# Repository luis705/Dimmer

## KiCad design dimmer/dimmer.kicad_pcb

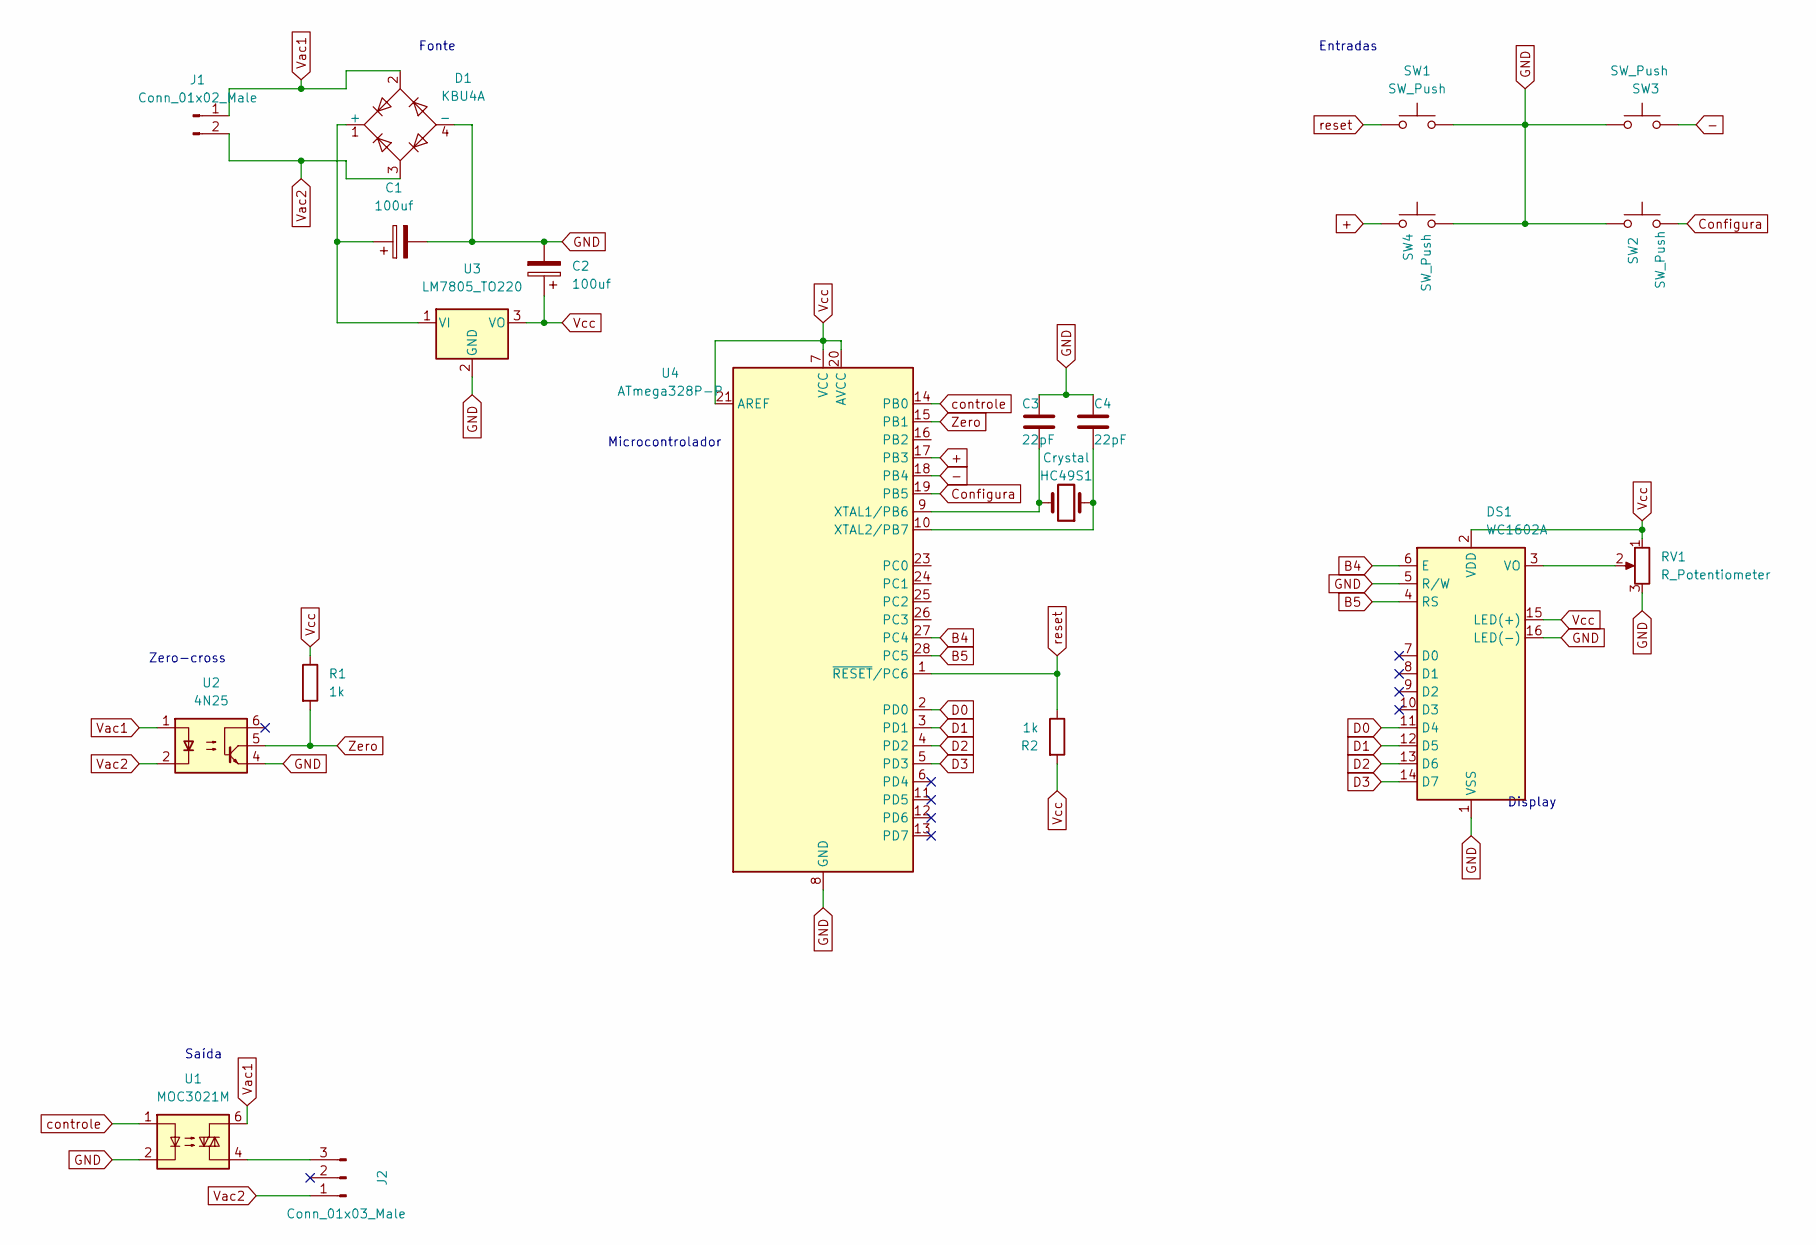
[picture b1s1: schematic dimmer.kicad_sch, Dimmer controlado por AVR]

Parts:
C1, C2: 100uf; CP_Radial_D8.0mm_P5.00mm
C3, C4: 22pF; C_Disc_D5.0mm_W2.5mm_P5.00mm
D1: KBU4A; Diode_Bridge_15.1x15.1x6.3mm_P10.9mm
DS1: WC1602A
HC49S1: Crystal; Crystal_HC49-4H_Vertical
J1: Conn_01x02_Male; Molex_KK-254_AE-6410-02A_1x02_P2.54mm_Vertical
J2: Conn_01x03_Male; FanPinHeader_1x03_P2.54mm_Vertical
R1, R2: 1k; R_Axial_DIN0204_L3.6mm_D1.6mm_P5.08mm_Horizontal
RV1: R_Potentiometer; Potentiometer_Runtron_RM-065_Vertical
SW1, SW2, SW3, SW4: SW_Push; SW_PUSH_6mm
U1: MOC3021M; DIP-6_W7.62mm
U2: 4N25; DIP-6_W7.62mm
U3: LM7805_TO220; TO-220-3_Vertical
U4: ATmega328P-P; DIP-28_W7.62mm

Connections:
+: SW4.2, U4.17 (PB3)
-: SW3.2, U4.18 (PB4)
B4: DS1.6 (E), U4.27 (PC4)
B5: DS1.4 (RS), U4.28 (PC5)
Configura: SW2.2, U4.19 (PB5)
D0: DS1.11 (D4), U4.2 (PD0)
D1: DS1.12 (D5), U4.3 (PD1)
D2: DS1.13 (D6), U4.4 (PD2)
D3: DS1.14 (D7), U4.5 (PD3)
GND: C1.2, C2.2, C3.1, C4.1, D1.4 (-), DS1.1 (VSS), DS1.5 (R/W), DS1.16 (LED(-)), RV1.3, SW1.1, SW2.1, SW3.1, SW4.1, U1.2, U2.4, U3.2 (GND), U4.8 (GND), U4.22 (GND)
unnamed: C1.1, D1.1 (+), U3.1 (VI)
unnamed: C3.2, HC49S1.2, U4.9 (XTAL1/PB6)
unnamed: C4.2, HC49S1.1, U4.10 (XTAL2/PB7)
unnamed: DS1.3 (VO), RV1.2
unnamed: J2.3, U1.4
Vac1: D1.2, J1.1, U1.6, U2.1
Vac2: D1.3, J1.2, J2.1, U2.2
Vcc: C2.1, DS1.2 (VDD), DS1.15 (LED(+)), R1.1, R2.2, RV1.1, U3.3 (VO), U4.7 (VCC), U4.20 (AVCC), U4.21 (AREF)
Zero: R1.2, U2.5, U4.15 (PB1)
controle: U1.1, U4.14 (PB0)
reset: R2.1, SW1.2, U4.1 (~RESET/PC6)

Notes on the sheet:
Zero-cross
Fonte
Microcontrolador
Saída
Display
Entradas

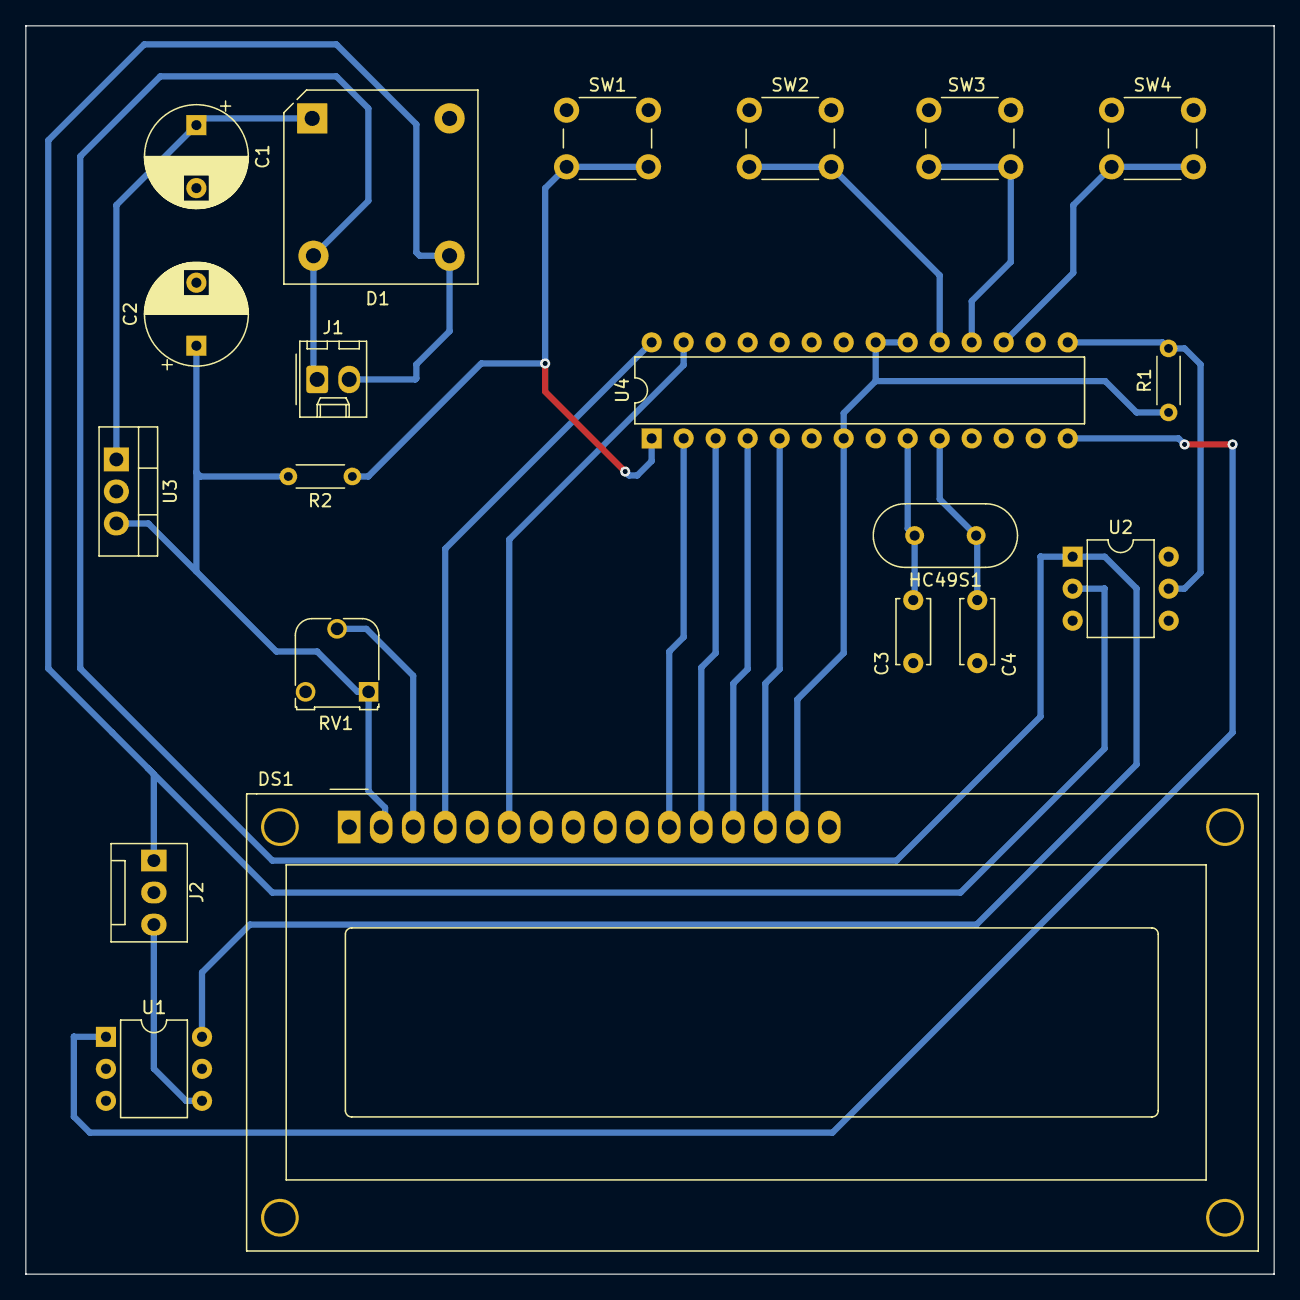
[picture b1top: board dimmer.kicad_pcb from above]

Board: 2 copper layers, 99.1 x 99.1 mm, 20 parts (0 on the bottom side), 21 nets.

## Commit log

2022-05-23 Criado gitignore
2022-05-23 Adicionado circuito inicial
